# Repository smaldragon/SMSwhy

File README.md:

# SMSwhy

This is an alternate Sega Master System motherboard in a 10cmX10cm format.

## Why

Felt like it

## Should I use it

Short Answer: No. It's 100% untested and I'm not sure there is even enough clearance for cartridges to plug in

## What can I do with this?

It's released under the unlicense, so feel free to modify it to your heart's content. You can also use the schematic for a resonable-sized board if you want. But remember: This is all untested and might have mistakes, so uh, double check everything if you go that route.

## What revisions is this board compatible with?

This was designed for the chips present in the "Master System II Power Base RGB" (the later french revision which lacks IC9), with a Alex Kidd bios. The output is RGB via scart.

## What additional chips are here that weren't in the original board?

A AMS1117 5volt regulator and a THS7375 video amplifier, both are SMD parts and still active as of writing of this readme

## Any additions?

It has a RESET button, a PAL/NTSC selector switch, room for a power LED, and some 1.27mm headers that could be used to install a (custom) designed FM board.

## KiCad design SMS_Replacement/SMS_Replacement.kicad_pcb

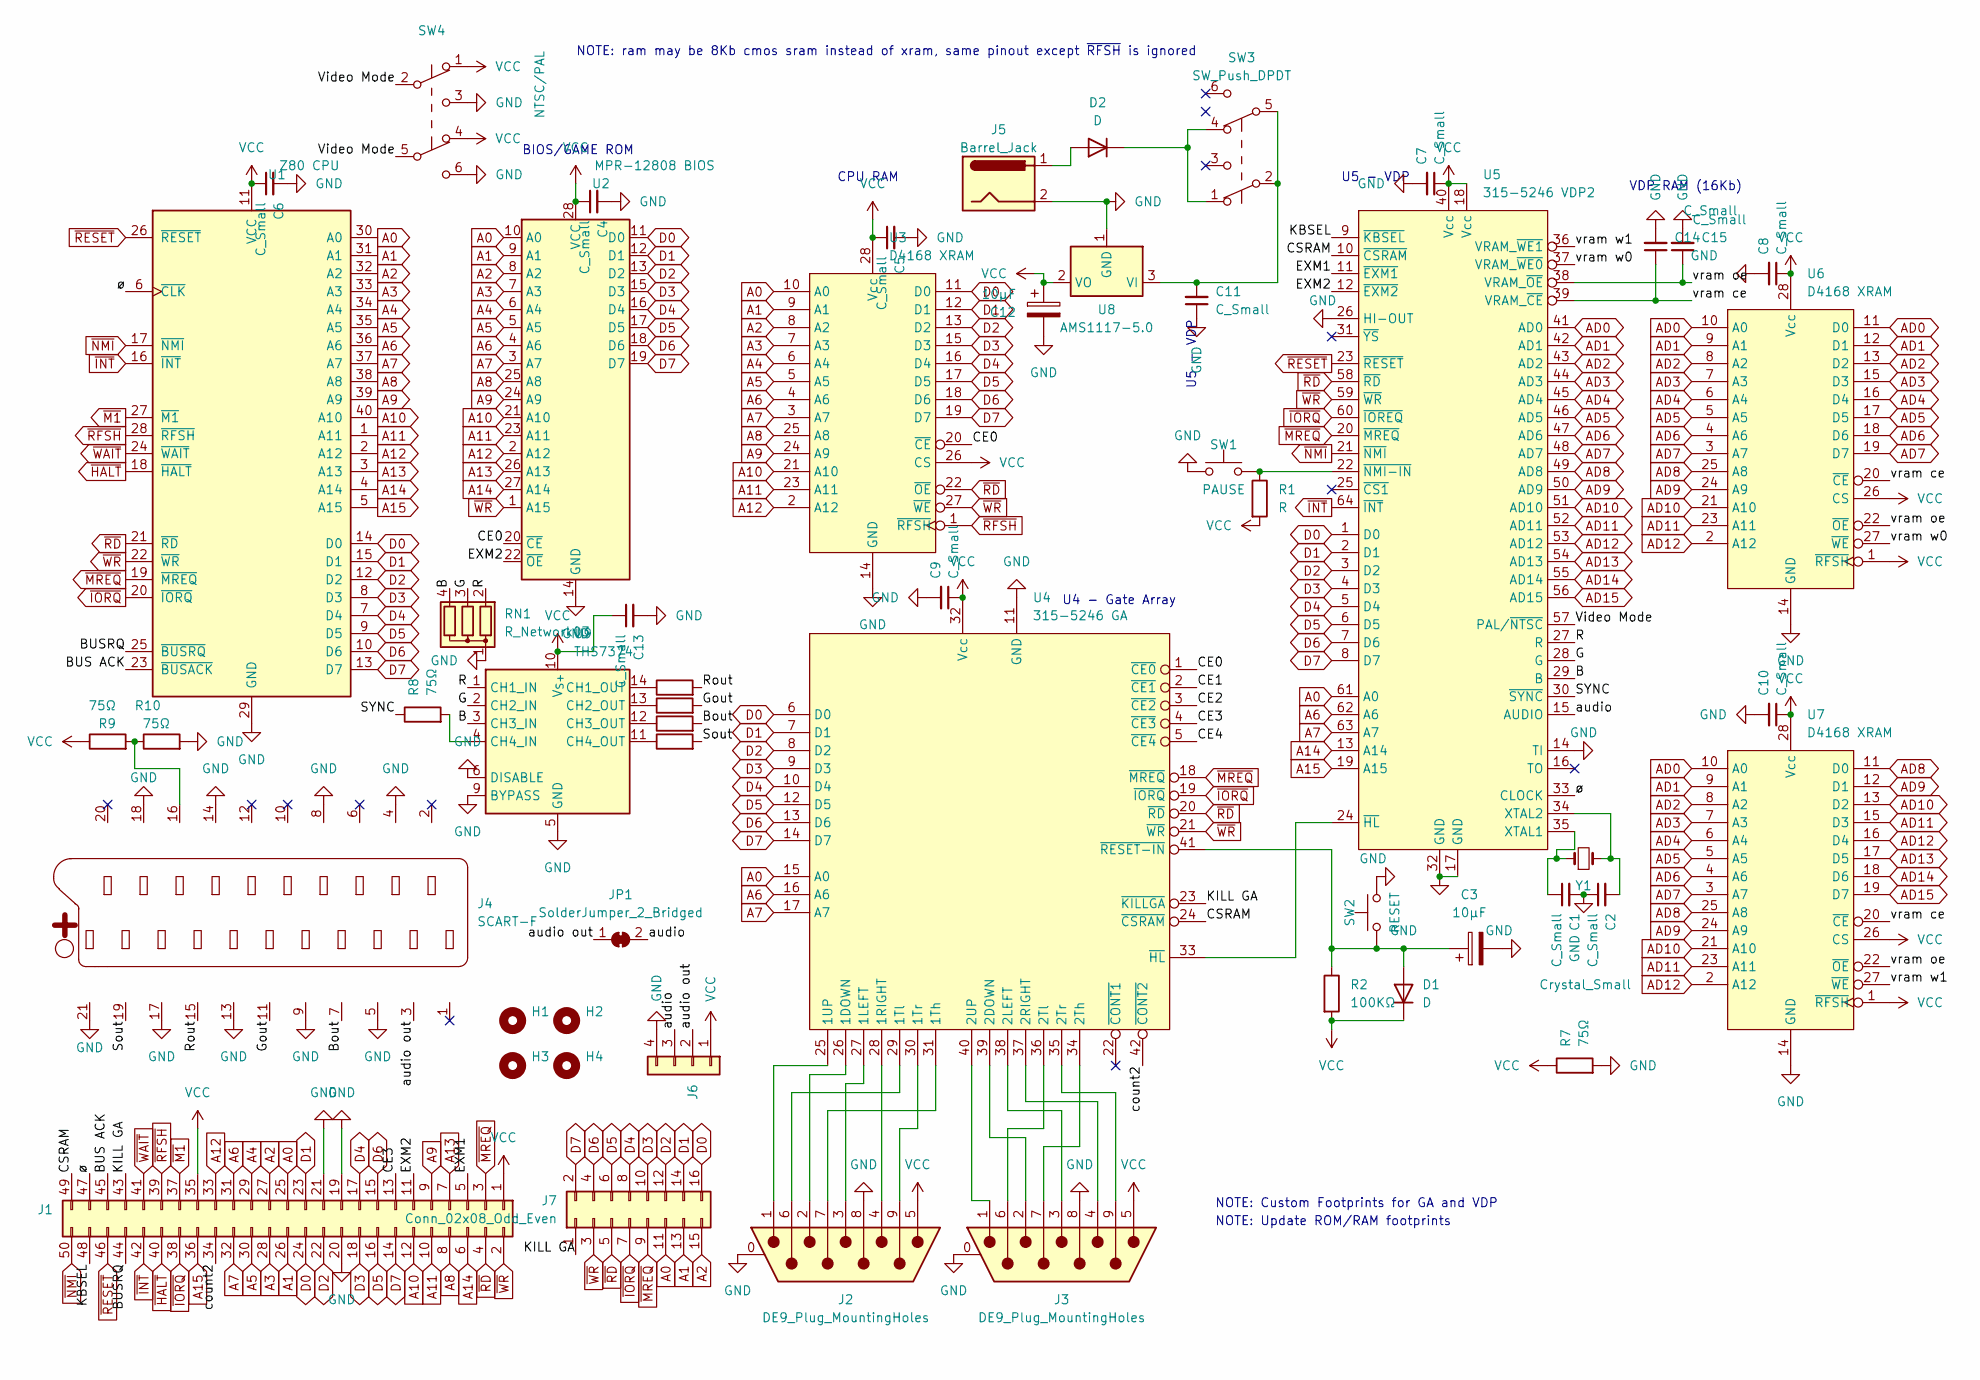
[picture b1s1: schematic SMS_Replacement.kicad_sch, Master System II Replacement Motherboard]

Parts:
C1, C2, C11: C_Small; C_Disc_D3.0mm_W1.6mm_P2.50mm
C3, C12: 10µF; CP_Radial_D4.0mm_P2.00mm
C4, C5, C6, C7, C8, C9, C10, C13, C14, C15: C_Small; C_1206_3216Metric
D1, D2: D; D_DO-34_SOD68_P2.54mm_Vertical_AnodeUp
H1, H2, H3, H4: MountingHole; MountingHole_3.2mm_M3_DIN965
J1: Conn_02x25_Odd_Even; PinHeader_2x25_P2.54mm_Vertical
J2, J3: DE9_Plug_MountingHoles; DSUB-9_Female_Horizontal_P2.77x2.84mm_EdgePinOffset4.94mm_H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
J4: SCART-F; SCART
J5: Barrel_Jack; BarrelJack_Kycon_KLDX-0202-xC_Horizontal
J6: Conn_01x04; PinHeader_1x04_P1.27mm_Vertical_SMD_Pin1Left
J7: Conn_02x08_Odd_Even; PinHeader_2x08_P1.27mm_Vertical_SMD
JP1: SolderJumper_2_Bridged; SolderJumper-2_P1.3mm_Bridged_Pad1.0x1.5mm
R1: R; R_Axial_DIN0204_L3.6mm_D1.6mm_P7.62mm_Horizontal
R2: 100KΩ; R_Axial_DIN0204_L3.6mm_D1.6mm_P1.90mm_Vertical
R3, R4, R5, R6, R7, R8, R9, R10: 75Ω; R_Axial_DIN0204_L3.6mm_D1.6mm_P1.90mm_Vertical
RN1: R_Network03; R_Array_SIP4
SW1: PAUSE; SW_PUSH_6mm_H13mm
SW2: RESET; SW_PUSH_6mm_H13mm
SW3: SW_Push_DPDT; SW_CuK_JS202011AQN_DPDT_Angled
SW4: NTSC/PAL; SW_CuK_JS202011AQN_DPDT_Angled
U1: Z80 CPU; DIP-40_W15.24mm_Socket
U2: MPR-12808 BIOS; DIP-28_W15.24mm_Socket
U3, U6, U7: D4168 XRAM; DIP-28_W15.24mm_Socket
U4: 315-5246 GA; SDIP-42
U5: 315-5246 VDP2; QIP-64_W22.86mm_Socket
U8: AMS1117-5.0; SOT-223-3_TabPin2
U9: THS7374; TSSOP-14_4.4x5mm_P0.65mm
Y1: Crystal_Small; Crystal_HC49-U_Vertical

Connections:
/B: RN1.4 (R3), U5.29 (B), U9.3 (CH3_IN)
/BUS ACK: J1.45, U1.23 (~BUSACK)
/BUSRQ: J1.44, U1.25 (~BUSRQ)
/Bout: J4.7, R4.2
/CE0: U2.20 (~CE), U3.20 (~CE), U4.1 (~CE0)
/CE1: U4.2 (~CE1)
/CE2: U4.3 (~CE2)
/CE3: J1.13, U4.4 (~CE3)
/CE4: U4.5 (~CE4)
/CSRAM: J1.49, U4.24 (~CSRAM), U5.10 (~CSRAM)
/EXM1: J1.5, U5.11 (~EXM1)
/EXM2: J1.11, U2.22 (~OE), U5.12 (~EXM2)
/G: RN1.3 (R2), U5.28 (G), U9.2 (CH2_IN)
/Gout: J4.11, R5.2
/KBSEL: J1.48, U5.9 (~KBSEL)
/KILL GA: J1.43, J7.1, U4.23 (~KILLGA)
/R: RN1.2 (R1), U5.27 (R), U9.1 (CH1_IN)
/Rout: J4.15, R6.2
/SYNC: R8.1, U5.30 (~SYNC)
/Sout: J4.19, R3.2
/Video Mode: SW4.2 (B), SW4.5 (B), U5.57 (PAL/~NTSC)
/audio: J6.3, JP1.2 (B), U5.15 (AUDIO)
/audio out: J4.3, J6.2, JP1.1 (A)
/count2: J1.34, U4.42 (~CONT2)
/vram ce: C14.1, U5.39 (VRAM_~CE), U6.20 (~CE), U7.20 (~CE)
/vram oe: C15.1, U5.38 (VRAM_~OE), U6.22 (~OE), U7.22 (~OE)
/vram w0: U5.37 (VRAM_~WE0), U6.27 (~WE)
/vram w1: U5.36 (VRAM_~WE1), U7.27 (~WE)
/ø: J1.47, U1.6 (~CLK), U5.33 (CLOCK)
A0: J1.25, J7.11, U1.30 (A0), U2.10 (A0), U3.10 (A0), U4.15 (A0), U5.61 (A0)
A1: J1.26, J7.13, U1.31 (A1), U2.9 (A1), U3.9 (A1)
A2: J1.27, J7.15, U1.32 (A2), U2.8 (A2), U3.8 (A2)
A3: J1.28, U1.33 (A3), U2.7 (A3), U3.7 (A3)
A4: J1.29, U1.34 (A4), U2.6 (A4), U3.6 (A4)
A5: J1.30, U1.35 (A5), U2.5 (A5), U3.5 (A5)
A6: J1.31, U1.36 (A6), U2.4 (A6), U3.4 (A6), U4.16 (A6), U5.62 (A6)
A7: J1.32, U1.37 (A7), U2.3 (A7), U3.3 (A7), U4.17 (A7), U5.63 (A7)
A8: J1.8, U1.38 (A8), U2.25 (A8), U3.25 (A8)
A9: J1.9, U1.39 (A9), U2.24 (A9), U3.24 (A9)
A10: J1.12, U1.40 (A10), U2.21 (A10), U3.21 (A10)
A11: J1.10, U1.1 (A11), U2.23 (A11), U3.23 (A11)
A12: J1.33, U1.2 (A12), U2.2 (A12), U3.2 (A12)
A13: J1.7, U1.3 (A13), U2.26 (A13)
A14: J1.6, U1.4 (A14), U2.27 (A14), U5.13 (A14)
A15: J1.36, U1.5 (A15), U5.19 (A15)
AD0: U5.41 (AD0), U6.10 (A0), U6.11 (D0), U7.10 (A0)
AD1: U5.42 (AD1), U6.9 (A1), U6.12 (D1), U7.9 (A1)
AD2: U5.43 (AD2), U6.8 (A2), U6.13 (D2), U7.8 (A2)
AD3: U5.44 (AD3), U6.7 (A3), U6.15 (D3), U7.7 (A3)
AD4: U5.45 (AD4), U6.6 (A4), U6.16 (D4), U7.6 (A4)
AD5: U5.46 (AD5), U6.5 (A5), U6.17 (D5), U7.5 (A5)
AD6: U5.47 (AD6), U6.4 (A6), U6.18 (D6), U7.4 (A6)
AD7: U5.48 (AD7), U6.3 (A7), U6.19 (D7), U7.3 (A7)
AD8: U5.49 (AD8), U6.25 (A8), U7.11 (D0), U7.25 (A8)
AD9: U5.50 (AD9), U6.24 (A9), U7.12 (D1), U7.24 (A9)
AD10: U5.51 (AD10), U6.21 (A10), U7.13 (D2), U7.21 (A10)
AD11: U5.52 (AD11), U6.23 (A11), U7.15 (D3), U7.23 (A11)
AD12: U5.53 (AD12), U6.2 (A12), U7.2 (A12), U7.16 (D4)
AD13: U5.54 (AD13), U7.17 (D5)
AD14: U5.55 (AD14), U7.18 (D6)
AD15: U5.56 (AD15), U7.19 (D7)
D0: J1.24, J7.16, U1.14 (D0), U2.11 (D0), U3.11 (D0), U4.6 (D0), U5.1 (D0)
D1: J1.23, J7.14, U1.15 (D1), U2.12 (D1), U3.12 (D1), U4.7 (D1), U5.2 (D1)
D2: J1.22, J7.12, U1.12 (D2), U2.13 (D2), U3.13 (D2), U4.8 (D2), U5.3 (D2)
D3: J1.18, J7.10, U1.8 (D3), U2.15 (D3), U3.15 (D3), U4.9 (D3), U5.4 (D3)
D4: J1.17, J7.8, U1.7 (D4), U2.16 (D4), U3.16 (D4), U4.10 (D4), U5.5 (D4)
D5: J1.16, J7.6, U1.9 (D5), U2.17 (D5), U3.17 (D5), U4.12 (D5), U5.6 (D5)
D6: J1.15, J7.4, U1.10 (D6), U2.18 (D6), U3.18 (D6), U4.13 (D6), U5.7 (D6)
D7: J1.14, J7.2, U1.13 (D7), U2.19 (D7), U3.19 (D7), U4.14 (D7), U5.8 (D7)
GND: C1.2, C2.1, C3.2, C4.2, C5.2, C6.2, C7.2, C8.2, C9.2, C10.2, C11.1, C12.2, C13.2, C14.2, C15.2, J1.19, J1.20, J1.21, J2.0 (PAD), J2.8, J3.0 (PAD), J3.8, J4.4, J4.5, J4.8, J4.9, J4.13, J4.14, J4.17, J4.18, J4.21, J5.2, J6.4, R7.2, R10.2, RN1.1 (common), SW1.1, SW2.2, SW4.3 (C), SW4.6 (C), U1.29 (GND), U2.14 (GND), U3.14 (GND), U4.11 (GND), U5.14 (TI), U5.17 (GND), U5.26 (HI-OUT), U5.32 (GND), U6.14 (GND), U7.14 (GND), U8.1 (GND), U9.5 (GND), U9.6 (DISABLE), U9.9 (BYPASS)
unnamed: C3.1, D1.2 (A), R2.1, SW2.1, U4.41 (~RESET-IN)
unnamed: D2.2 (A), J5.1
unnamed: D2.1 (K), SW3.1 (A), SW3.4 (A)
unnamed: J4.16, R9.2, R10.1
unnamed: J2.2, U4.26 (1DOWN)
unnamed: J2.3, U4.27 (1LEFT)
unnamed: J2.4, U4.28 (1RIGHT)
unnamed: J2.7, U4.31 (1Th)
unnamed: J2.6, U4.29 (1Tl)
unnamed: J2.9, U4.30 (1Tr)
unnamed: J2.1, U4.25 (1UP)
unnamed: J3.2, U4.39 (2DOWN)
unnamed: J3.3, U4.38 (2LEFT)
unnamed: J3.4, U4.37 (2RIGHT)
unnamed: J3.7, U4.34 (2Th)
unnamed: J3.6, U4.36 (2Tl)
unnamed: J3.9, U4.35 (2Tr)
unnamed: J3.1, U4.40 (2UP)
unnamed: U4.33 (~HL), U5.24 (~HL)
unnamed: C1.1, U5.35 (XTAL1), Y1.1
unnamed: C2.2, U5.34 (XTAL2), Y1.2
unnamed: R1.1, SW1.2, U5.22 (~NMI-IN)
unnamed: C11.2, SW3.2 (B), SW3.5 (B), U8.3 (VI)
unnamed: R6.1, U9.14 (CH1_OUT)
unnamed: R5.1, U9.13 (CH2_OUT)
unnamed: R4.1, U9.12 (CH3_OUT)
unnamed: R8.2, U9.4 (CH4_IN)
unnamed: R3.1, U9.11 (CH4_OUT)
VCC: C4.1, C5.1, C6.1, C7.1, C8.1, C9.1, C10.1, C12.1, C13.1, D1.1 (K), J1.1, J1.35, J2.5, J3.5, J6.1, R1.2, R2.2, R7.1, R9.1, SW4.1 (A), SW4.4 (A), U1.11 (VCC), U2.28 (VCC), U3.26 (CS), U3.28 (Vcc), U4.32 (Vcc), U5.18 (Vcc), U5.40 (Vcc), U6.1 (~RFSH), U6.26 (CS), U6.28 (Vcc), U7.1 (~RFSH), U7.26 (CS), U7.28 (Vcc), U8.2 (VO), U9.10 (V_{S+})
~HALT: J1.40, U1.18 (~HALT)
~INT: J1.42, U1.16 (~INT), U5.64 (~INT)
~IORQ: J1.38, J7.7, U1.20 (~IORQ), U4.19 (~IORQ), U5.60 (~IOREQ)
~M1: J1.37, U1.27 (~M1)
~MREQ: J1.3, J7.9, U1.19 (~MREQ), U4.18 (~MREQ), U5.20 (~MREQ)
~NMI: J1.50, U1.17 (~NMI), U5.21 (~NMI)
~RD: J1.4, J7.5, U1.21 (~RD), U3.22 (~OE), U4.20 (~RD), U5.58 (~RD)
~RESET: J1.46, U1.26 (~RESET), U5.23 (~RESET)
~RFSH: J1.39, U1.28 (~RFSH), U3.1 (~RFSH)
~WAIT: J1.41, U1.24 (~WAIT)
~WR: J1.2, J7.3, U1.22 (~WR), U2.1 (A15), U3.27 (~WE), U4.21 (~WR), U5.59 (~WR)

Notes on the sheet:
U4 - Gate Array
BIOS/GAME ROM
VDP RAM (16Kb)
U5 - VDP
CPU RAM
NOTE: ram may be 8Kb cmos sram instead of xram, same pinout except ~{RFSH} is ignored
NOTE: Custom Footprints for GA and VDP
NOTE: Update ROM/RAM footprints

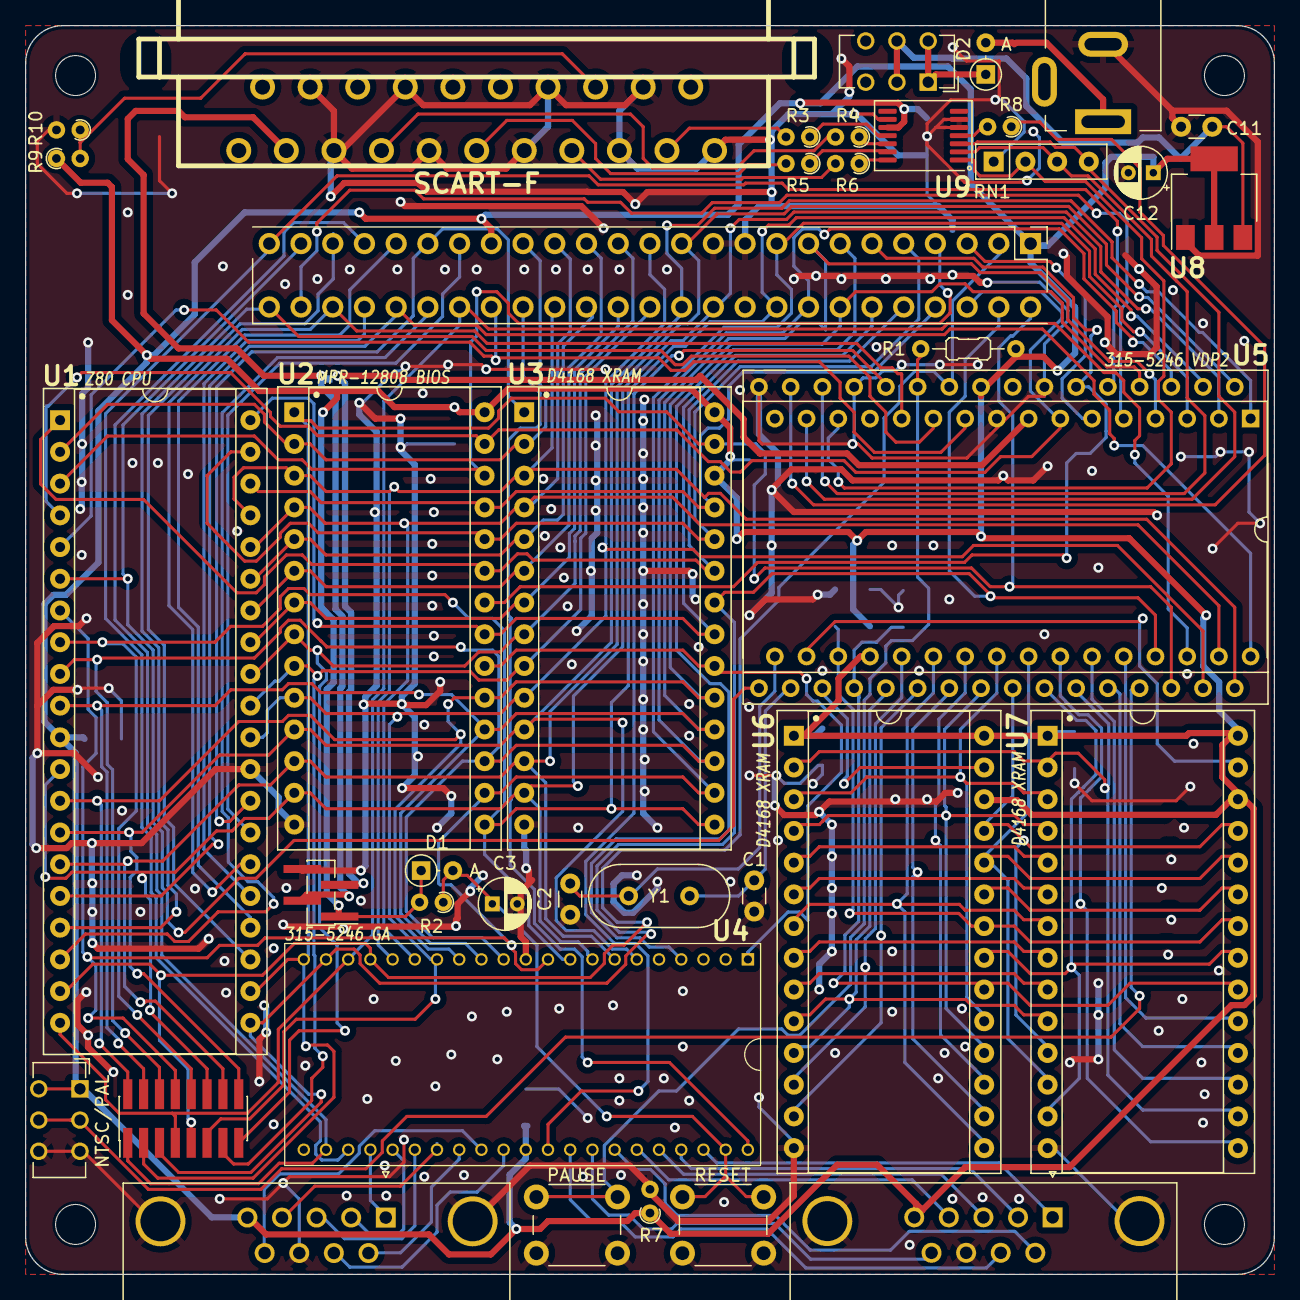
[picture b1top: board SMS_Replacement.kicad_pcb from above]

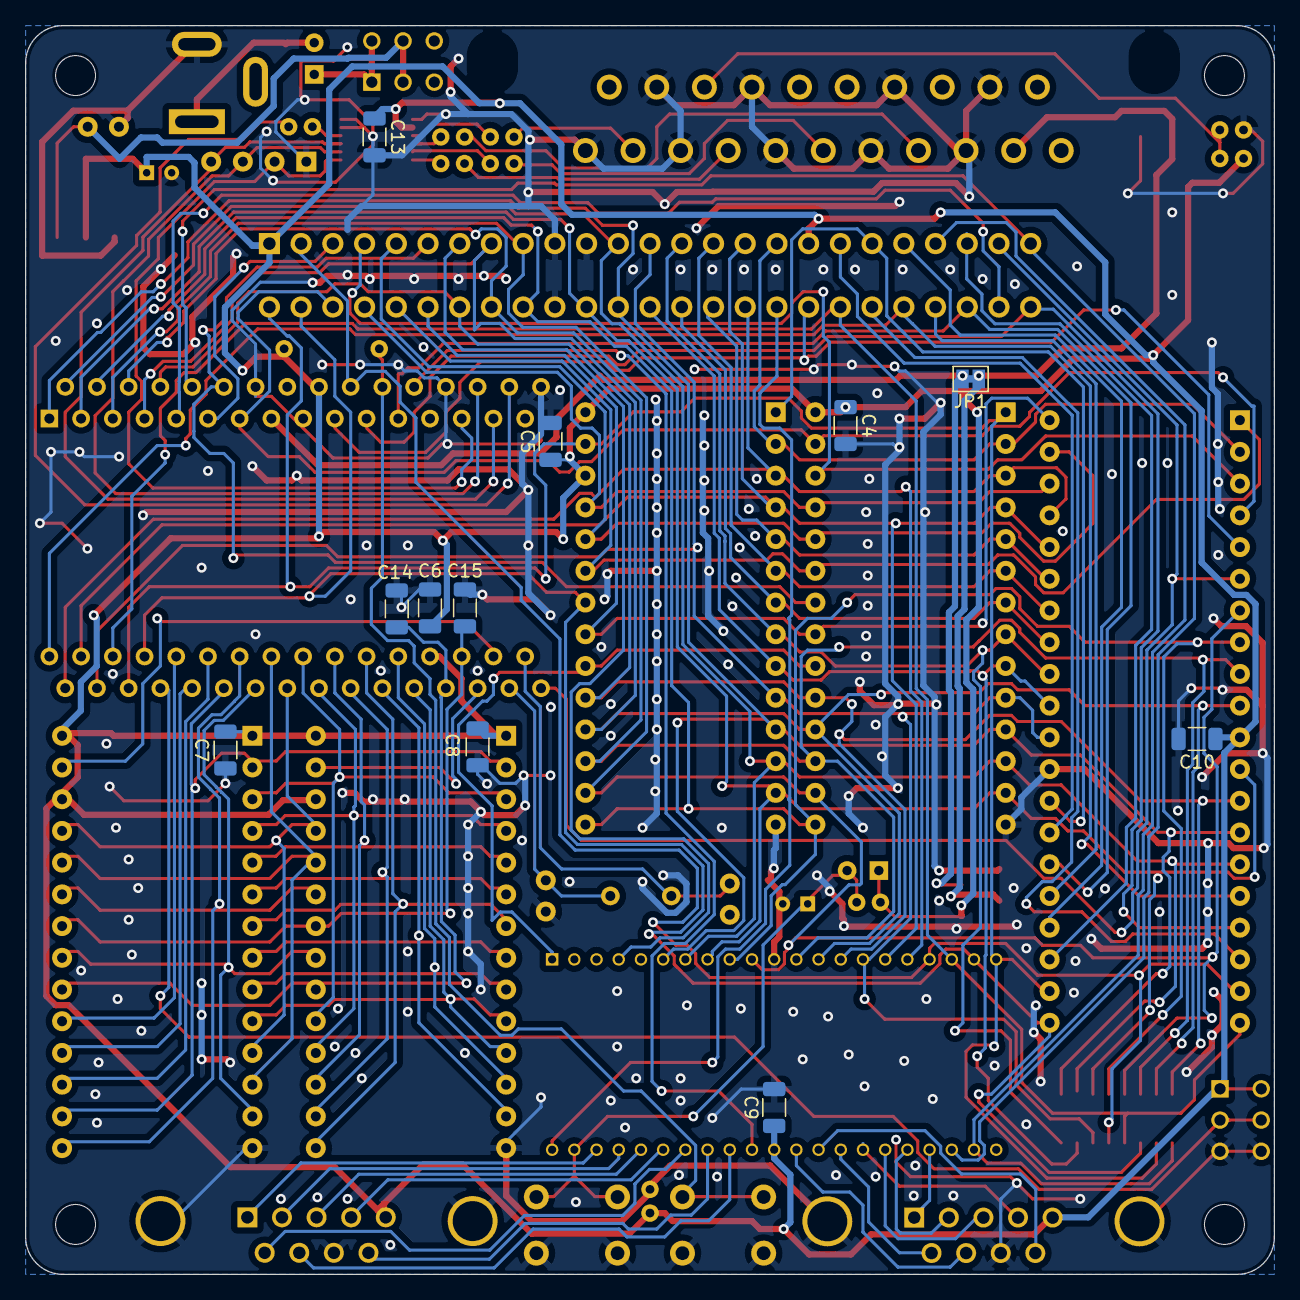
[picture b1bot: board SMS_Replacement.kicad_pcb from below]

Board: 4 copper layers, 100.0 x 100.0 mm, 54 parts (11 on the bottom side), 107 nets.

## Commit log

2023-12-19 add readme and data
